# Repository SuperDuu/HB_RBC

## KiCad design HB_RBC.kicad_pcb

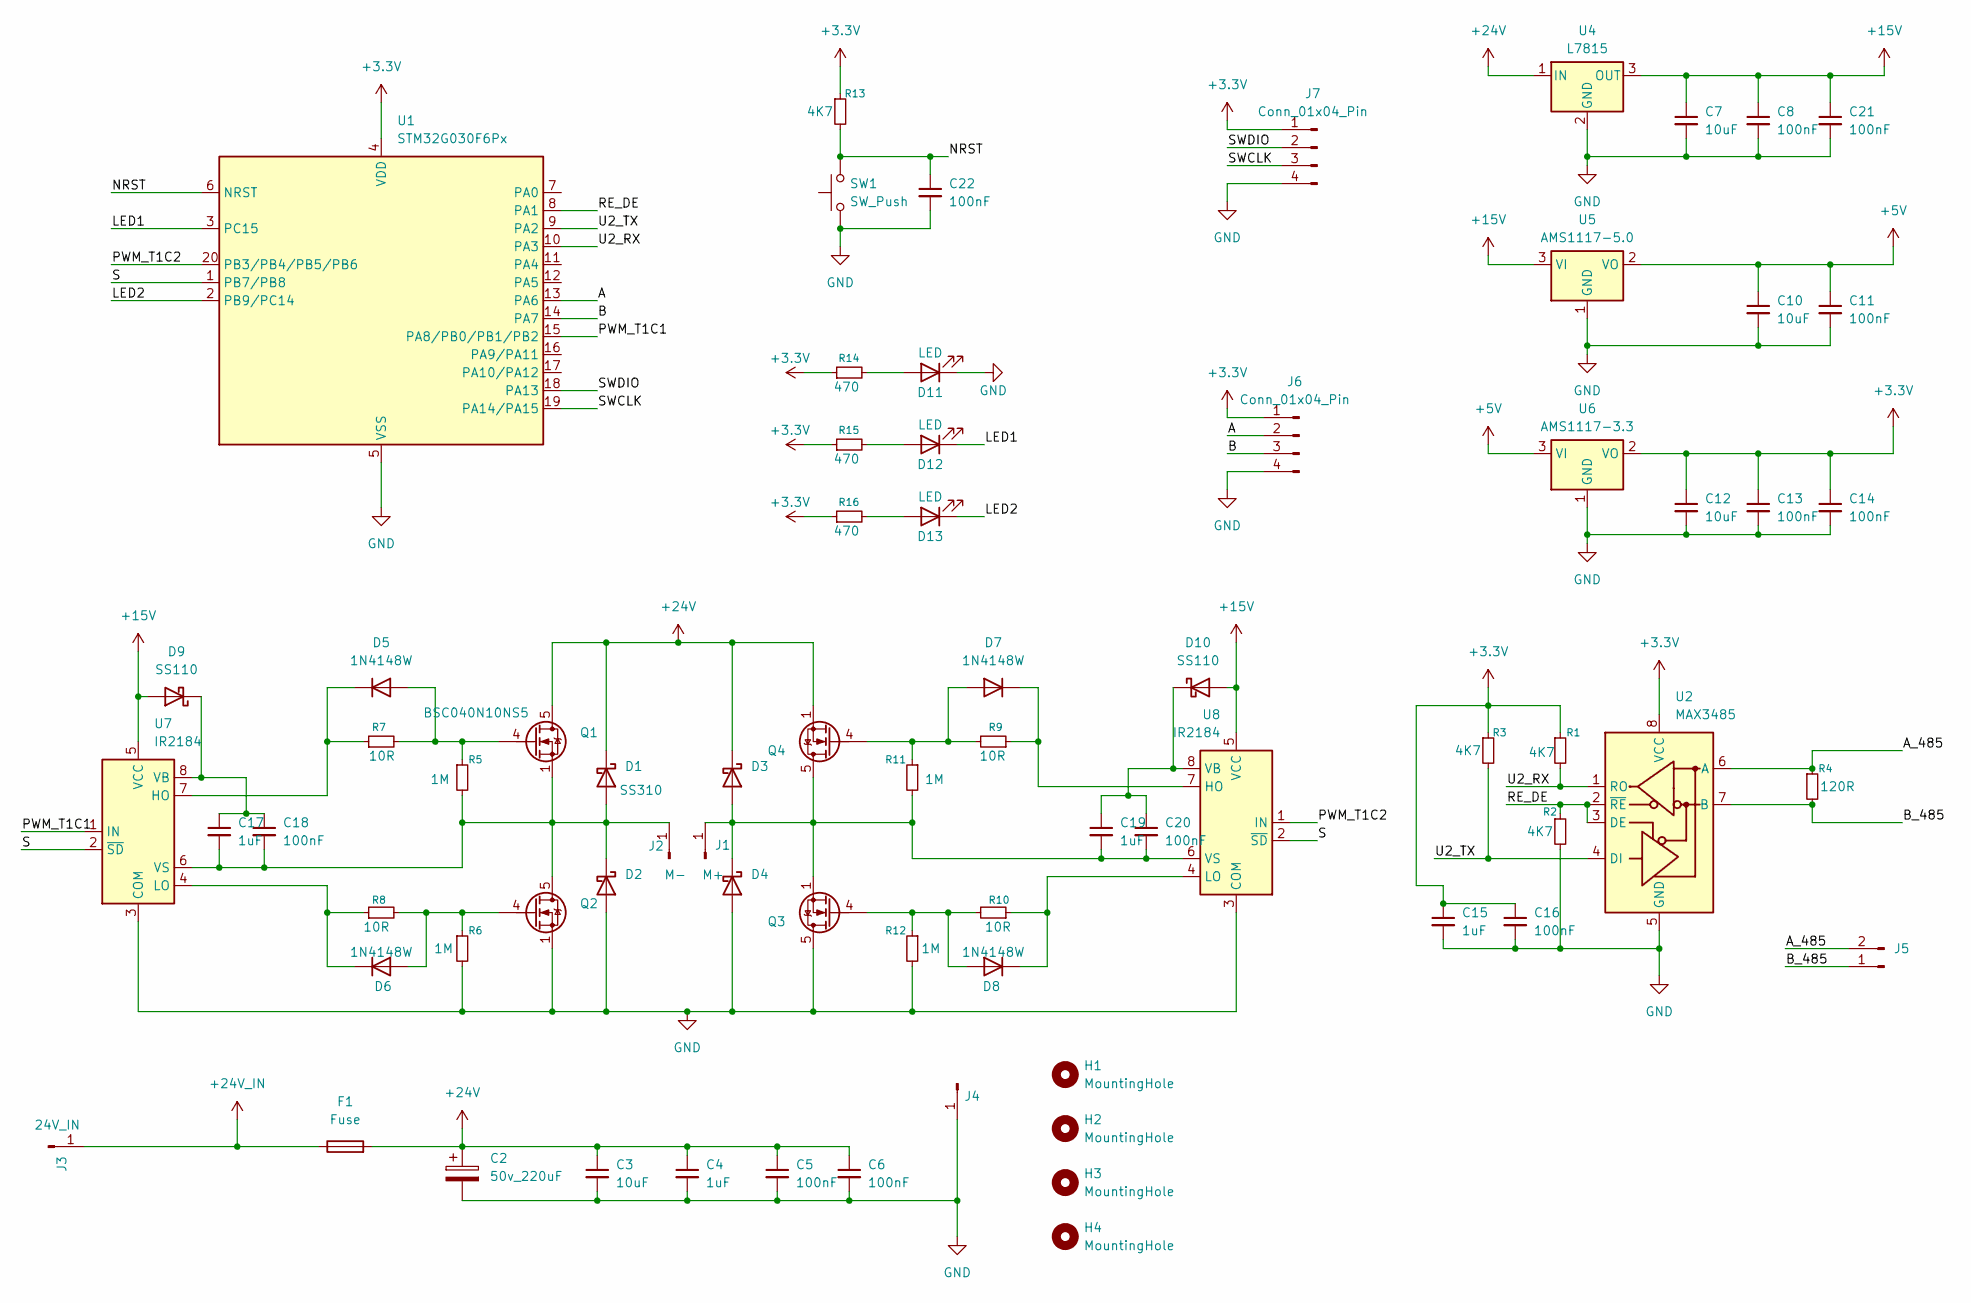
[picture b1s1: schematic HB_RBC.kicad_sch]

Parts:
C2: 50v_220uF; CP_Elec_10x10.5
C3, C7, C10, C12: 10uF; C_0805_2012Metric_Pad1.18x1.45mm_HandSolder
C4, C15, C17, C19: 1uF; C_0805_2012Metric_Pad1.18x1.45mm_HandSolder
C5, C6, C8, C11, C13, C14, C16, C18, C20, C21, C22: 100nF; C_0805_2012Metric_Pad1.18x1.45mm_HandSolder
D1: SS310; D_SMA
D2, D3, D4: D_Schottky; D_SMA
D5, D6, D7, D8: 1N4148W; D_SOD-123
D9, D10: SS110; D_SMA
D11, D12, D13: LED; LED_0805_2012Metric_Pad1.15x1.40mm_HandSolder
F1: Fuse; Fuseholder_Cylinder-5x20mm_Schurter_0031_8201_Horizontal_Op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
H1, H2, H3, H4: MountingHole; MountingHole_3.2mm_M3_ISO14580_Pad_TopBottom
J1: M+; SolderWirePad_1x01_SMD_4x8mm
J2: M-; SolderWirePad_1x01_SMD_4x8mm
J3: 24V_IN; SolderWirePad_1x01_SMD_4x8mm
J4: Conn_01x01_Pin; SolderWirePad_1x01_SMD_4x8mm
J5: Conn_01x02_Pin; JST_XH_S2B-XH-A-1_1x02_P2.50mm_Horizontal
J6, J7: Conn_01x04_Pin; JST_XH_S4B-XH-A-1_1x04_P2.50mm_Horizontal
Q1, Q2, Q3, Q4: BSC040N10NS5; TDSON-8-1
R1, R2, R3, R13: 4K7; R_0805_2012Metric_Pad1.20x1.40mm_HandSolder
R4: 120R; R_0805_2012Metric_Pad1.20x1.40mm_HandSolder
R5, R6, R11, R12: 1M; R_0805_2012Metric_Pad1.20x1.40mm_HandSolder
R7, R8, R9, R10: 10R; R_0805_2012Metric_Pad1.20x1.40mm_HandSolder
R14, R15, R16: 470; R_0805_2012Metric_Pad1.20x1.40mm_HandSolder
SW1: SW_Push; SW_Tactile_SPST_NO_Straight_CK_PTS636Sx25SMTRLFS
U1: STM32G030F6Px; TSSOP-20_4.4x6.5mm_P0.65mm
U2: MAX3485; SOIC-8_3.9x4.9mm_P1.27mm
U4: L7815; TO-263-3_TabPin2
U5: AMS1117-5.0; SOT-223-3_TabPin2
U6: AMS1117-3.3; SOT-223-3_TabPin2
U7, U8: IR2184; SOIC-8_3.9x4.9mm_P1.27mm

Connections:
+3.3V: C12.1, C13.1, C14.1, C15.1, C16.1, J6.1, J7.1, R1.1, R3.1, R13.1, R14.1, R15.1, R16.1, U1.4 (VDD), U2.8 (VCC), U6.2 (VO)
+5V: C10.1, C11.1, U5.2 (VO), U6.3 (VI)
+15V: C7.1, C8.1, C21.1, D9.2 (A), D10.2 (A), U4.3 (OUT), U5.3 (VI), U7.5 (VCC), U8.5 (VCC)
+24V: C2.1, C3.1, C4.1, C5.1, C6.1, D1.1 (K), D3.1 (K), F1.2, Q1.5 (D), Q4.1 (S), Q4.2 (S), Q4.3 (S), U4.1 (IN)
+24V_IN: F1.1, J3.1 (Pin_1_1)
/A: J6.2, U1.13 (PA6)
/A_485: J5.2, R4.1, U2.6 (A)
/B: J6.3, U1.14 (PA7)
/B_485: J5.1, R4.2, U2.7 (B)
/LED1: D12.1 (K), U1.3 (PC15)
/LED2: D13.1 (K), U1.2 (PB9/PC14)
/NRST: C22.1, R13.2, SW1.2, U1.6 (NRST)
/PWM_T1C1: U1.15 (PA8/PB0/PB1/PB2), U7.1 (IN)
/PWM_T1C2: U1.20 (PB3/PB4/PB5/PB6), U8.1 (IN)
/RE_DE: R2.1, U1.8 (PA1), U2.2 (~RE), U2.3 (DE)
/S: U1.1 (PB7/PB8), U7.2 (~SD), U8.2 (~SD)
/SWCLK: J7.3, U1.19 (PA14/PA15)
/SWDIO: J7.2, U1.18 (PA13)
/U2_RX: R1.2, U1.10 (PA3), U2.1 (RO)
/U2_TX: R3.2, U1.9 (PA2), U2.4 (DI)
GND: C2.2, C3.2, C4.2, C5.2, C6.2, C7.2, C8.2, C10.2, C11.2, C12.2, C13.2, C14.2, C15.2, C16.2, C21.2, C22.2, D2.2 (A), D4.2 (A), D11.1 (K), J4.1 (Pin_1_1), J6.4, J7.4, Q2.1 (S), Q2.2 (S), Q2.3 (S), Q3.5 (D), R2.2, R6.2, R12.2, SW1.1, U1.5 (VSS), U2.5 (GND), U4.2 (GND), U5.1 (GND), U6.1 (GND), U7.3 (COM), U8.3 (COM)
unnamed: C17.2, C18.2, D1.2 (A), D2.1 (K), J2.1 (Pin_1_1), Q1.1 (S), Q1.2 (S), Q1.3 (S), Q2.5 (D), R5.2, U7.6 (VS)
unnamed: C19.2, C20.2, D3.2 (A), D4.1 (K), J1.1 (Pin_1_1), Q3.1 (S), Q3.2 (S), Q3.3 (S), Q4.5 (D), R11.2, U8.6 (VS)
unnamed: D5.2 (A), Q1.4 (G), R5.1, R7.2
unnamed: D5.1 (K), R7.1, U7.7 (HO)
unnamed: D6.2 (A), Q2.4 (G), R6.1, R8.2
unnamed: D6.1 (K), R8.1, U7.4 (LO)
unnamed: D7.2 (A), Q4.4 (G), R9.2, R11.1
unnamed: D7.1 (K), R9.1, U8.7 (HO)
unnamed: D8.2 (A), Q3.4 (G), R10.2, R12.1
unnamed: D8.1 (K), R10.1, U8.4 (LO)
unnamed: C17.1, C18.1, D9.1 (K), U7.8 (VB)
unnamed: C19.1, C20.1, D10.1 (K), U8.8 (VB)
unnamed: D11.2 (A), R14.2
unnamed: D12.2 (A), R15.2
unnamed: D13.2 (A), R16.2

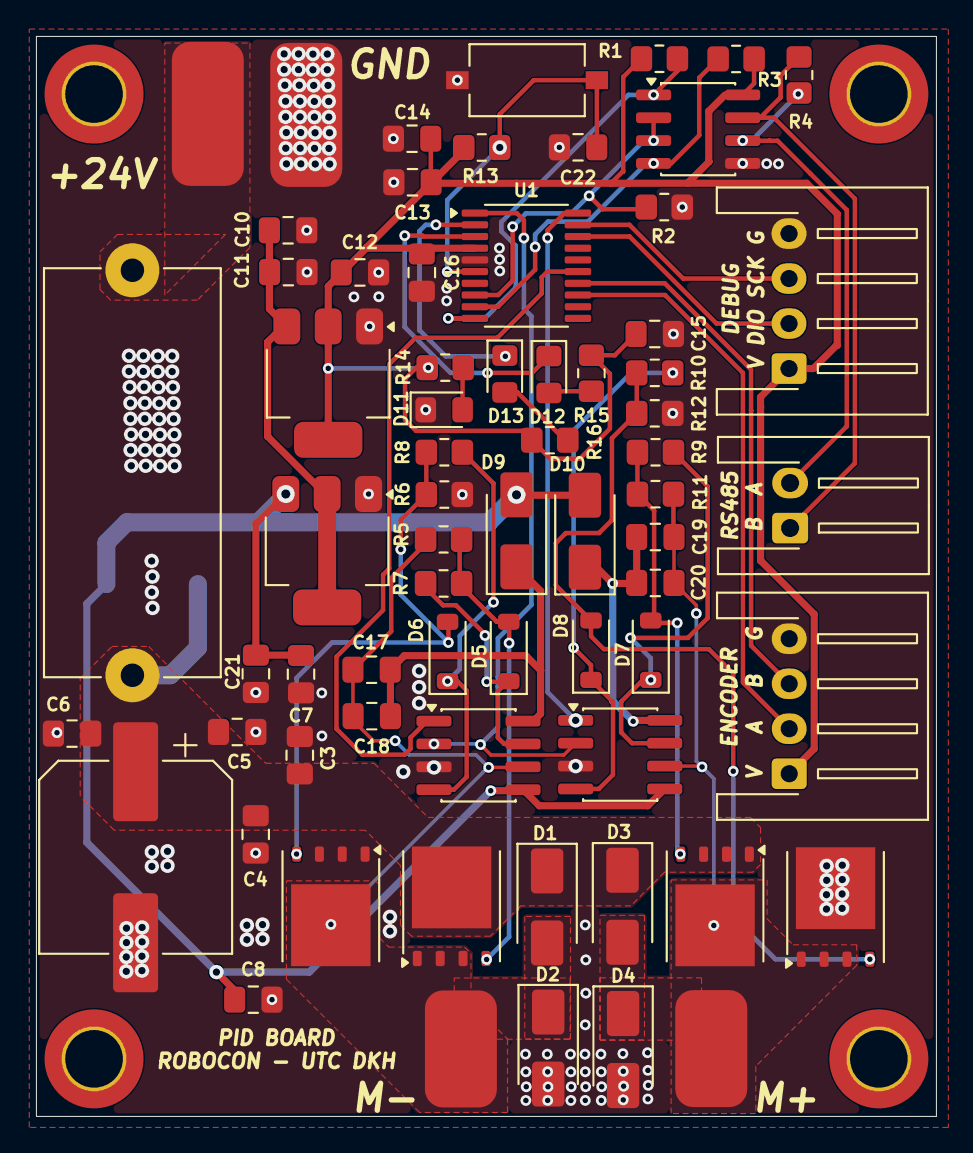
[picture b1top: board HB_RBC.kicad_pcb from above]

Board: 2 copper layers, 50.0 x 60.0 mm, 73 parts (1 on the bottom side), 36 nets.
